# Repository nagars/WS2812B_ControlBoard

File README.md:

# WS2812B_ControlBoard

A dedicated Power Supply and Controller PCB designed to safely power and control WS2812B addressable RGB LED strips using an onboard **ESP32 microcontroller**.

## Overview
A WS2812B LED Power supply and control board that can support power consumption of up to 3.5A (4A ceiling protected by a fuse) and wireless control using an esp32c6. Can connect up to 5 strips. 

### Power consumption calculation:
- 1 LED consumes 0.3W at max white light brightness. 
- Reducing to 1 colour consumes 0.1 W. 
- At 50% brightness, power consumption drops to 0.05W.
- As a result, in this configuration one can run a 300 LED strip at around 3A.

### Key Features
* **Integrated Power Management:** Safely splits 5V power supply between the high-current LED strip and the ESP32. Schottkey diode allows ESP32 to be powered by USB without powering other circuitry.
* **Blowout Protection:** 3.5A fuse prevents power supply from burning out.
* **ESP32 Powered:** Leverage built-in Wi-Fi and Bluetooth to connect your LED project to smart home ecosystems (WLED, Home Assistant, ESPHome).
* **Logic Level Shifting:** Level shifter to bump ESP32's 3.3V GPIO data signal to the 5V signal required by WS2812B strips (prevents flickering and data corruption over longer distances).
* **Decoupling Protection:** large electrolytic capacitors to absorb sudden voltage spikes that could damage the LEDs.

## Hardware Requirements & Recommendations

To fully utilize this board, you will need:
1. **Power Supply:** A high-quality 5V DC power supply capable of supplying enough Amperage for your specific LED strip length (Formula: `Number of LEDs × 0.06A = Total Amps needed`).
2. **WS2812B LED Strip:** 3-pin addressable strip (5V, Data, GND).
3. **Thick Gauge Wire:** For connecting the power supply to the PCB, and the PCB to the LED strips, minimizing voltage drop.

## Safety Warning

* **Double-check polarities:** No AC reverse polarity protection. Follow the silkscreen markers.
* **Heat Dissipation:** Watch for heating at high power loads.

### Schematic Layout V1/V2

### PCB Layout V1/V2

### Schematic Layout V3

### PCB Layout V3

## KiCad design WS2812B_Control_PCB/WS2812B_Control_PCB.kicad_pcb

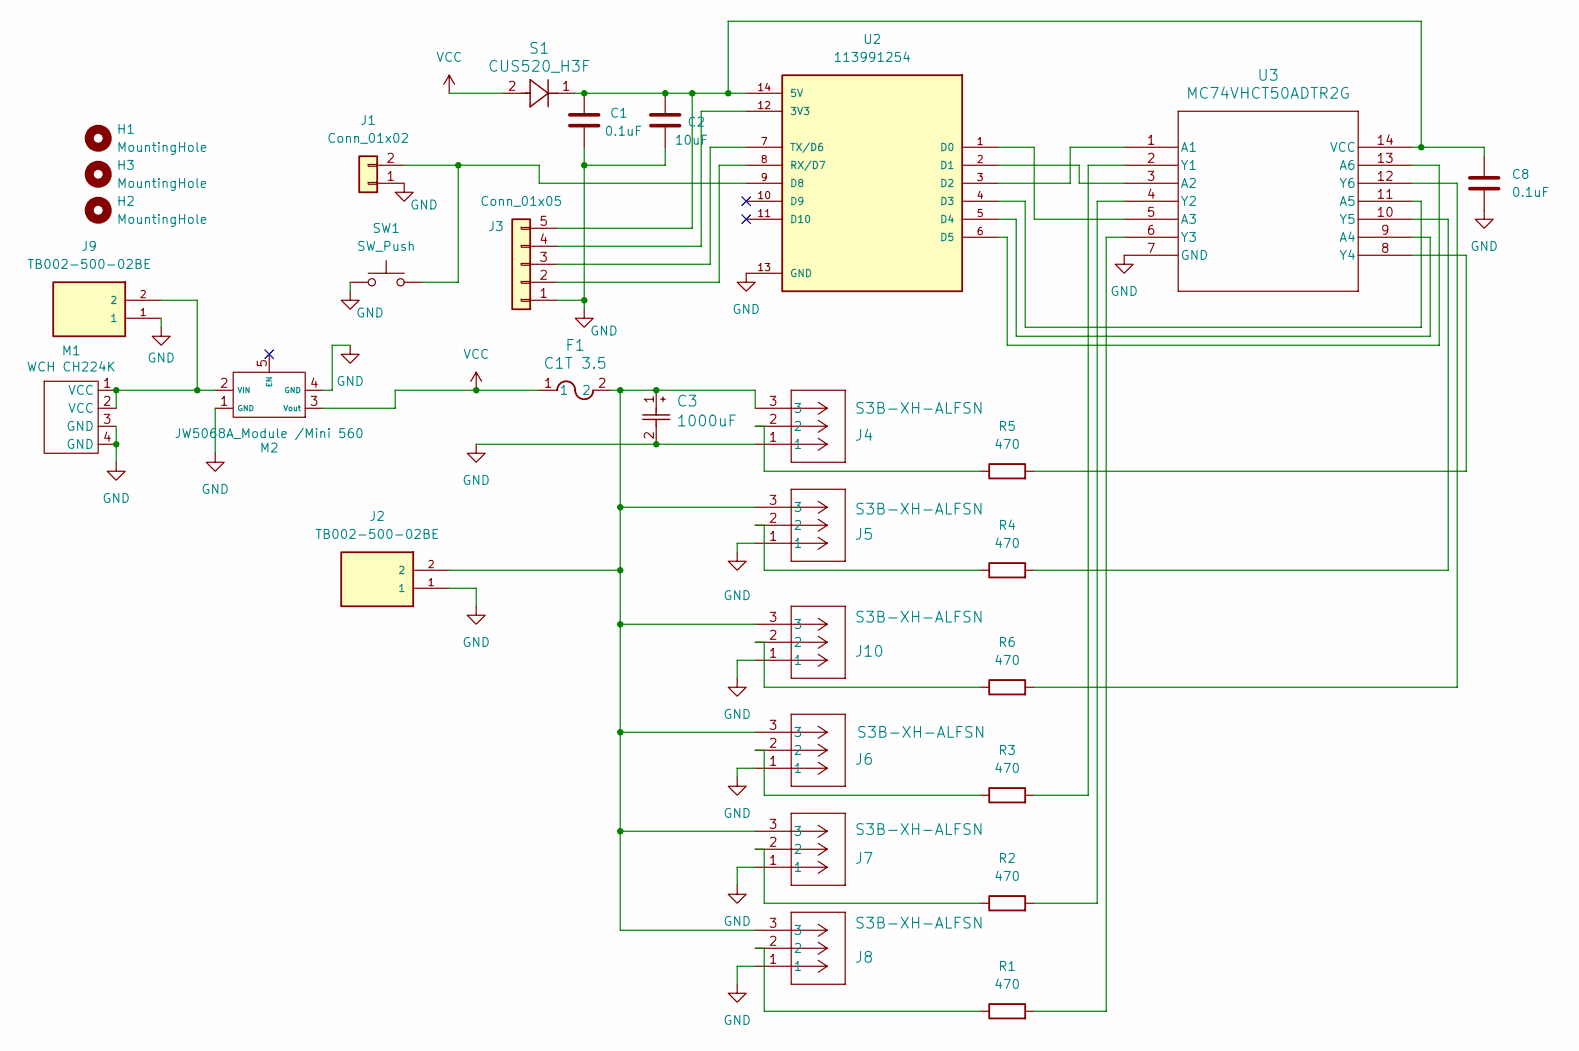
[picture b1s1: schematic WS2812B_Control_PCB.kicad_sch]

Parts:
C1, C8: 0.1uF; R_0402_1005Metric_Pad0.72x0.64mm_HandSolder
C2: 10uF; R_0402_1005Metric_Pad0.72x0.64mm_HandSolder
C3: 1000uF; CAP_RHA&slash_HS_8X11P7_NCH
F1: C1T 3.5; C1_BEL
H1, H2, H3: MountingHole; MountingHole_3.2mm_M3
J1: Conn_01x02; PinHeader_1x02_P2.54mm_Vertical
J2, J9: TB002-500-02BE; CUI_TB002-500-02BE
J3: Conn_01x05; PinHeader_1x05_P2.54mm_Vertical
J4, J5, J6, J7, J8, J10: S3B-XH-ALFSN; CONN_S3B-XH-ALFSN_JST
M1: WCH CH224K; WCH CH224K Module
M2: JW5068A_Module /Mini 560; JW5068A_Module
R1, R2, R3, R4, R5, R6: 470; RESC1005X40N
S1: CUS520_H3F; USC_TOS
SW1: SW_Push; SW_PUSH_6mm
U2: 113991254; XIAO-ESP32-C6-DIP; PARTREV v1.0
U3: MC74VHCT50ADTR2G; TSSOP14_4P50X5P10_ONS

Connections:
GND: C1.2, C2.2, C3.2, C8.2, J1.1, J2.1, J3.1, J4.1, J5.1, J6.1, J7.1, J8.1, J9.1, J10.1, M1.3 (GND), M1.4 (GND), M2.1 (GND), M2.4 (GND), SW1.1, U2.13 (GND), U3.7 (GND)
unnamed: C3.1, F1.2, J2.2, J4.3, J5.3, J6.3, J7.3, J8.3, J10.3
unnamed: J1.2, SW1.2, U2.9 (D8)
unnamed: J3.2, U2.8 (RX/D7)
unnamed: J3.3, U2.7 (TX/D6)
unnamed: J3.4, U2.12 (3V3)
unnamed: C1.1, C2.1, C8.1, J3.5, S1.1, U2.14 (5V), U3.14 (VCC)
unnamed: J4.2, R5.1
unnamed: J5.2, R4.1
unnamed: J6.2, R3.1
unnamed: J7.2, R2.1
unnamed: J8.2, R1.1
unnamed: J10.2, R6.1
unnamed: J9.2, M1.1 (VCC), M1.2 (VCC), M2.2 (VIN)
unnamed: U2.1 (D0), U3.5 (A3)
unnamed: U2.2 (D1), U3.3 (A2)
unnamed: U2.3 (D2), U3.1 (A1)
unnamed: U2.4 (D3), U3.11 (A5)
unnamed: U2.5 (D4), U3.9 (A4)
unnamed: U2.6 (D5), U3.13 (A6)
unnamed: R3.2, U3.2 (Y1)
unnamed: R2.2, U3.4 (Y2)
unnamed: R1.2, U3.6 (Y3)
unnamed: R5.2, U3.8 (Y4)
unnamed: R4.2, U3.10 (Y5)
unnamed: R6.2, U3.12 (Y6)
VCC: F1.1, M2.3 (Vout), S1.2

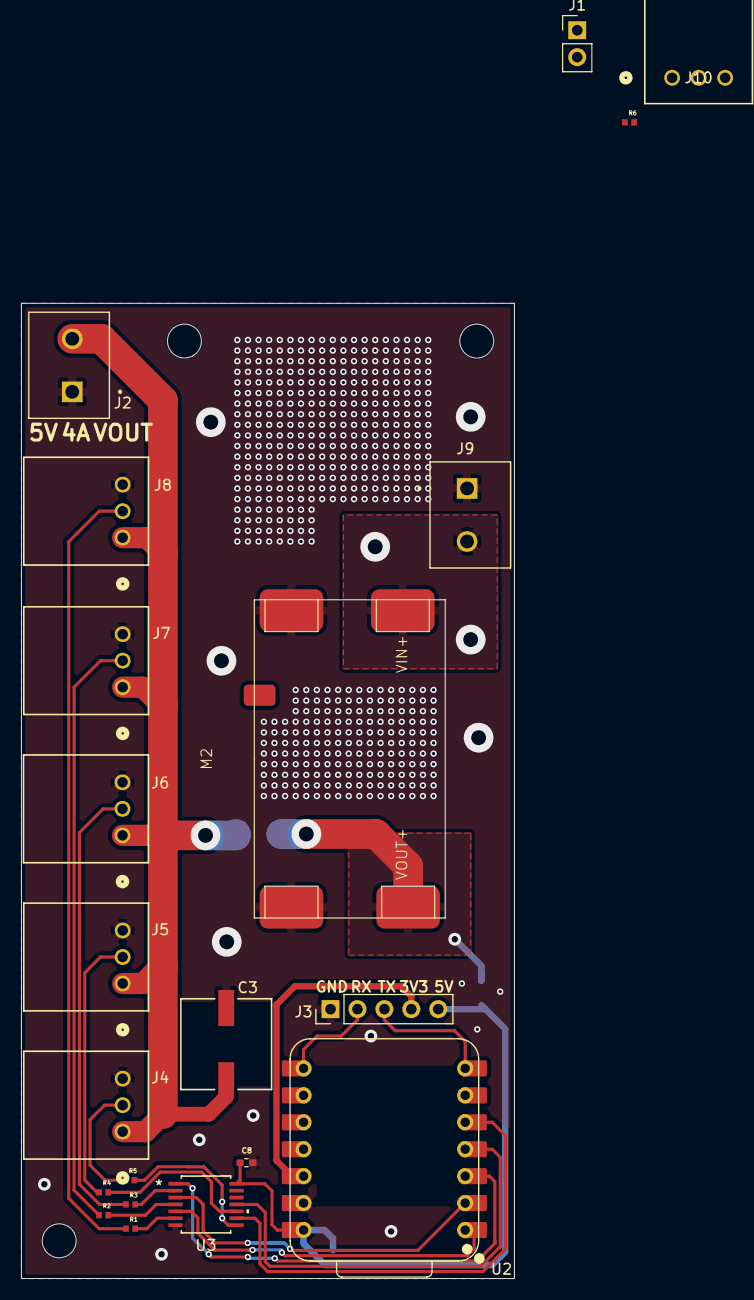
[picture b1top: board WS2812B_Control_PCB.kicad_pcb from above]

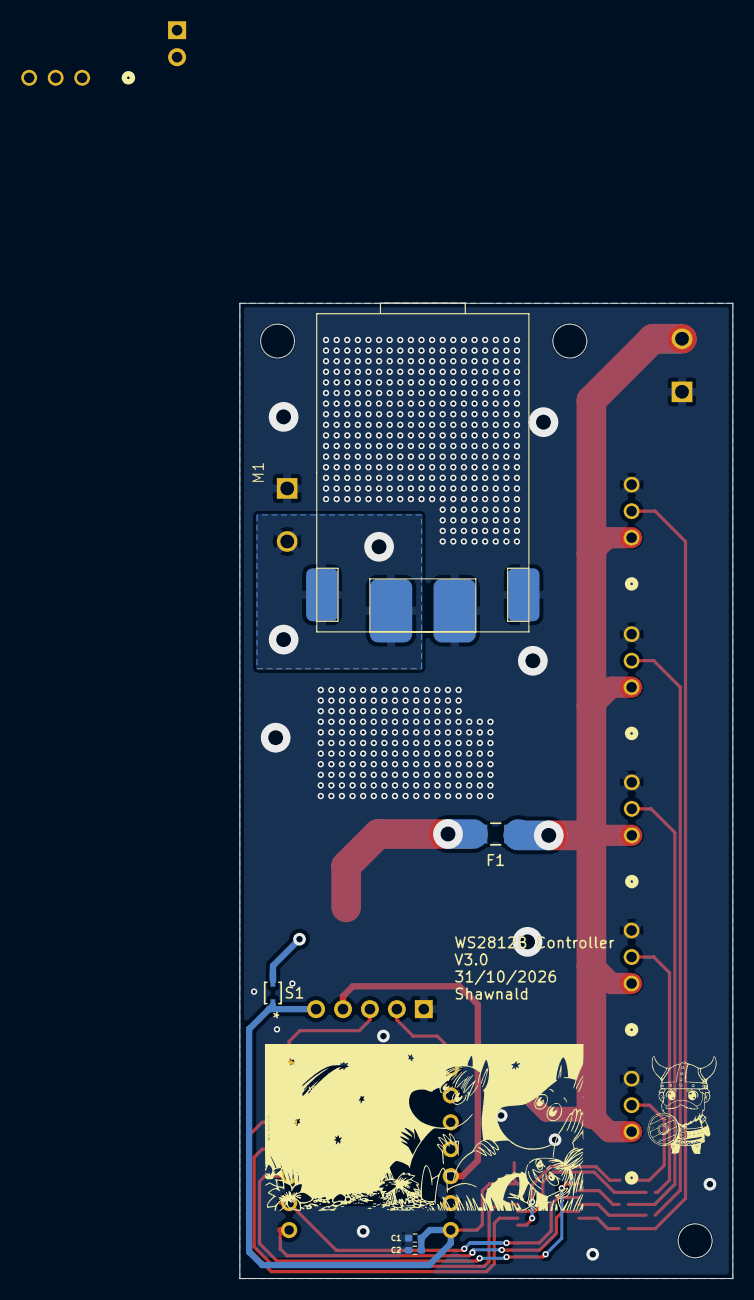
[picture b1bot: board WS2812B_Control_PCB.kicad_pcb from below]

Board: 2 copper layers, 46.5 x 91.9 mm, 29 parts (5 on the bottom side), 27 nets.
